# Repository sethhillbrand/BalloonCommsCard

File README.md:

# BalloonCommsCard
Dual-computer communications card designed to work with CSBF balloon flights

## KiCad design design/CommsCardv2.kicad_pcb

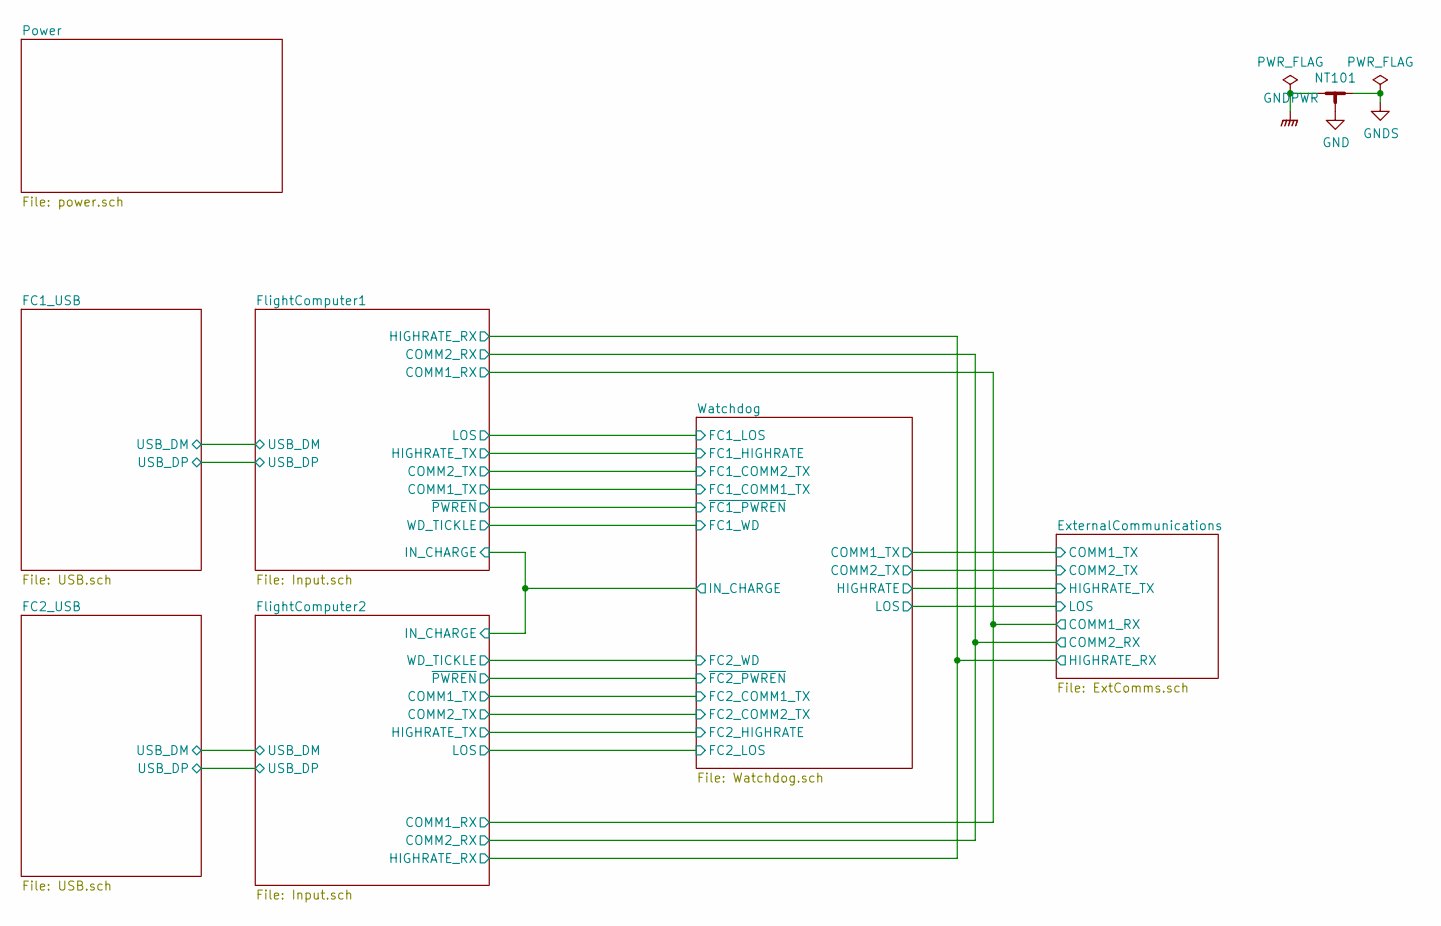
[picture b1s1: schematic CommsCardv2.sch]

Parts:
NT101: NP; NetTie-3_SMD_Pad2.0mm

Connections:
GND: NT101.3; also elsewhere on the board
GNDPWR: NT101.1; also elsewhere on the board

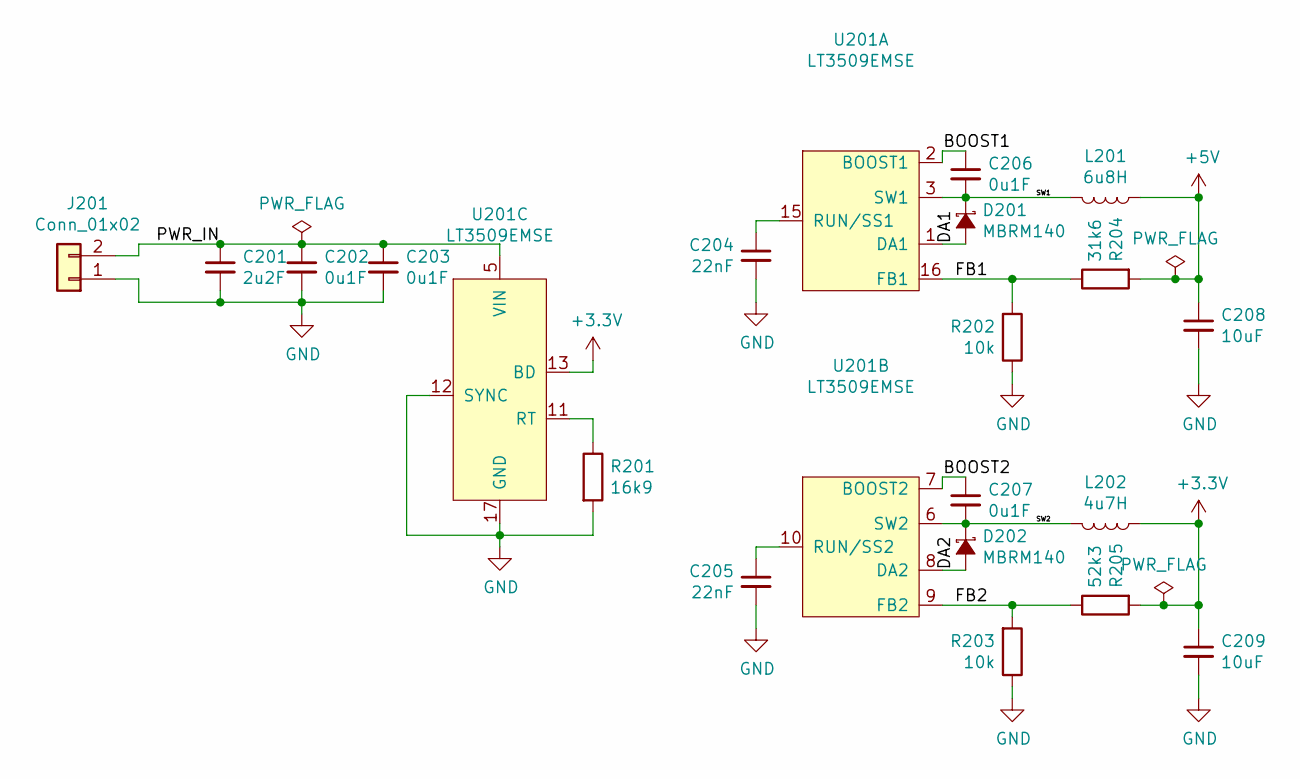
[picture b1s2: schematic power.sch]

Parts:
C201: 2u2F; C_0805_2012Metric; mpn UMK212BB7225KG-T
C202, C203, C206, C207: 0u1F; C_0603_1608Metric; mpn CL10B104KO8WPNC
C204, C205: 22nF; C_0603_1608Metric; mpn GRM188R71C223KA01D
C208, C209: 10uF; C_0805_2012Metric; mpn EMK212BB7106MG-T
D201, D202: MBRM140; D_Powermite2_AK; mpn MBRM140T3G
J201: Conn_01x02; PhoenixContact_MC_1,5_2-G-5.08_1x02_P5.08mm_Horizontal
L201: 6u8H; L_Abracon_ASPI-3012S; mpn ASPI-0315FS-6R8M-T2
L202: 4u7H; L_Abracon_ASPI-3012S; mpn ASPI-0315FS-4R7M-T2
R201: 16k9; R_0603_1608Metric; mpn ERJ-3EKF1692V
R202, R203: 10k; R_0603_1608Metric; mpn CRG0603J10K
R204: 31k6; R_0603_1608Metric; mpn CRCW060331K6FKEA
R205: 52k3; R_0603_1608Metric; mpn CRCW060352K3FKEA
U201: LT3509EMSE; MSOP-16-1EP_3x4mm_P0.5mm_EP1.65x2.85mm_ThermalVias; mpn LT3509EMSE#PBF

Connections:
+5V: C208.1, L201.1, R204.2; also elsewhere on the board
/Power/BOOST1: C206.1, U201.2 (BOOST1)
/Power/BOOST2: C207.1, U201.7 (BOOST2)
/Power/DA1: D201.2 (A), U201.1 (DA1)
/Power/DA2: D202.2 (A), U201.8 (DA2)
/Power/FB1: R202.2, R204.1, U201.16 (FB1)
/Power/FB2: R203.2, R205.1, U201.9 (FB2)
/Power/PWR_IN: C201.1, C202.1, C203.1, J201.2, U201.4 (VIN), U201.5 (VIN)
/Power/SW1: C206.2, D201.1 (K), L201.2, U201.3 (SW1)
/Power/SW2: C207.2, D202.1 (K), L202.2, U201.6 (SW2)
GND: C201.2, C202.2, C203.2, C204.2, C205.2, C208.2, C209.2, J201.1, R201.2, R202.1, R203.1, U201.12 (SYNC), U201.14 (GND), U201.17 (GND); also elsewhere on the board
unnamed: C204.1, U201.15 (RUN/SS1)
unnamed: C205.1, U201.10 (RUN/SS2)
unnamed: R201.1, U201.11 (RT)

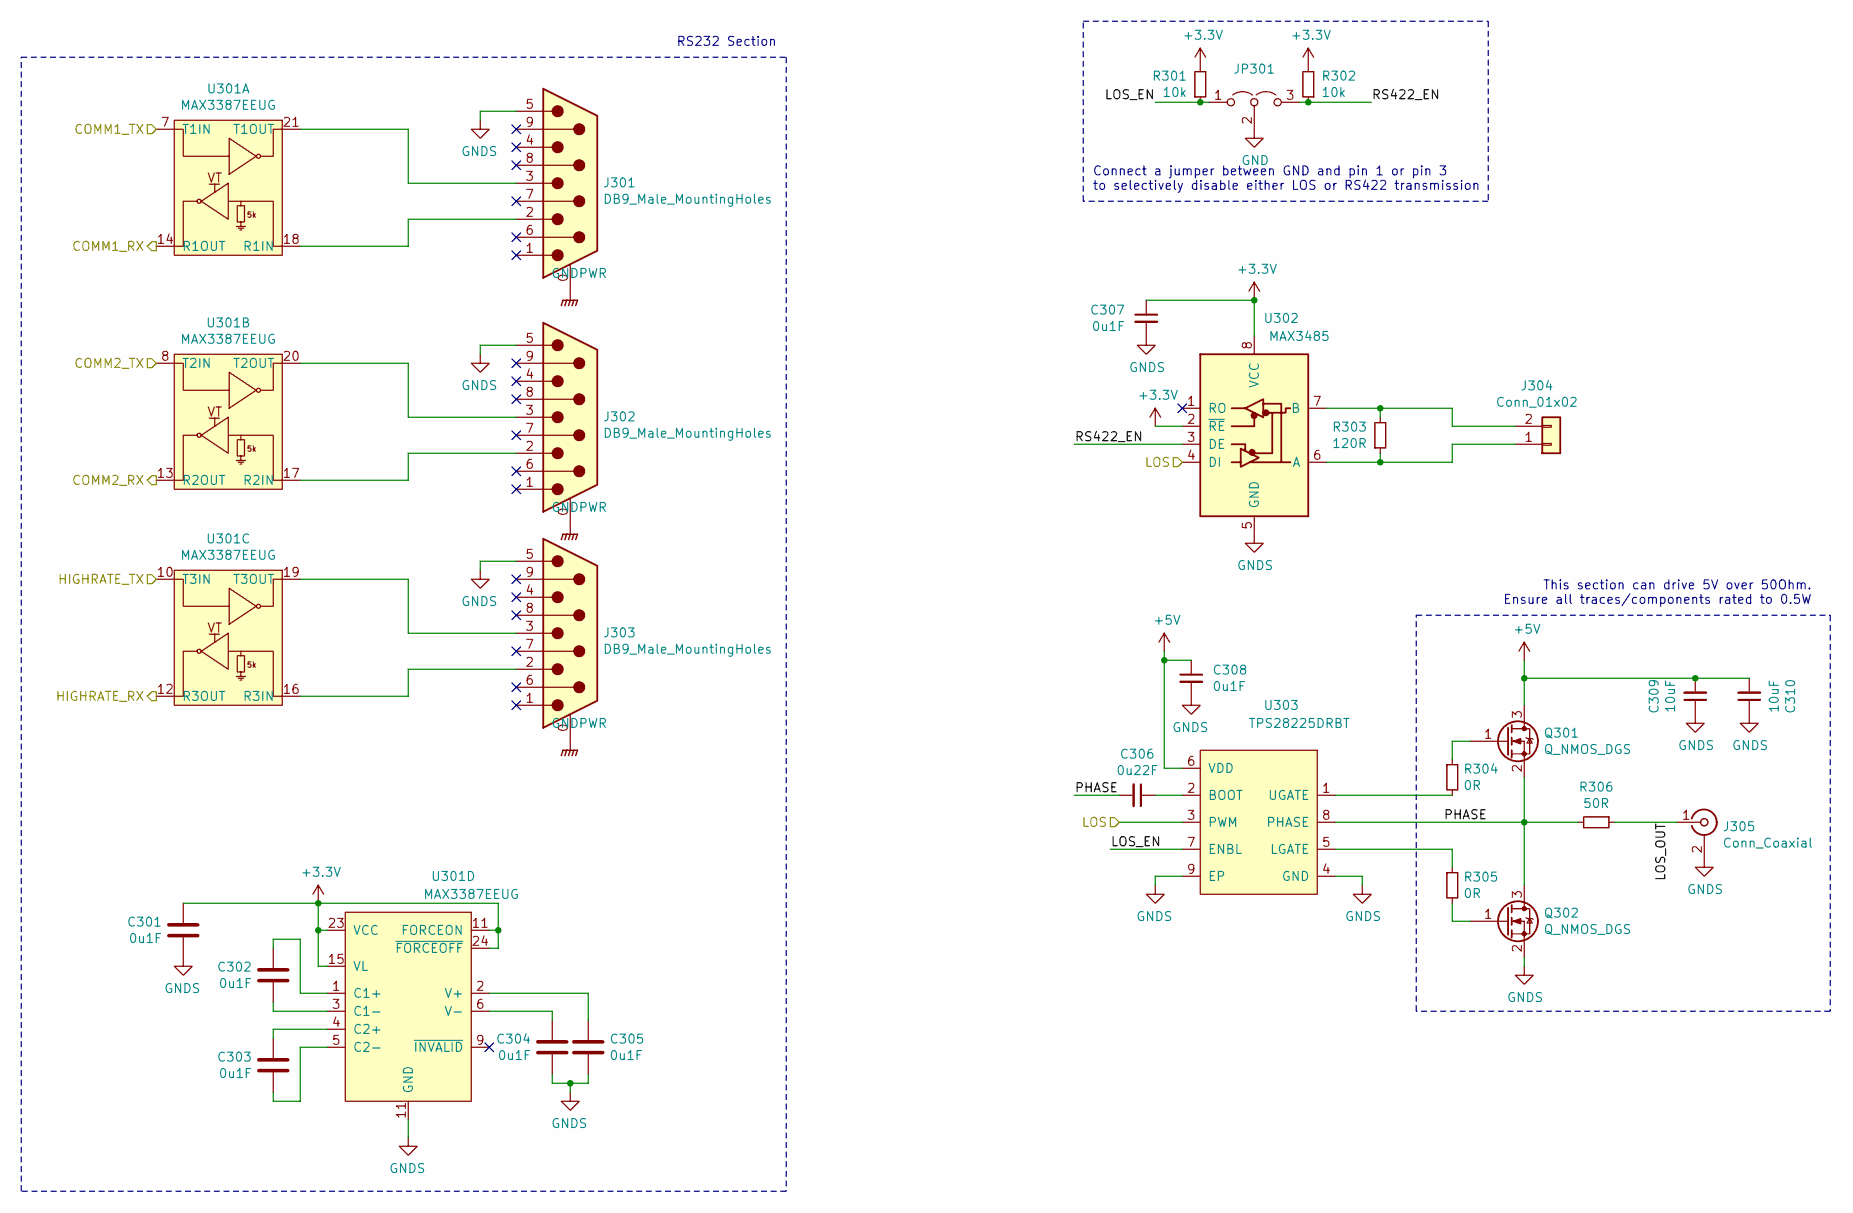
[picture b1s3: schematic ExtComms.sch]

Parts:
C301, C302, C303, C304, C305, C307, C308: 0u1F; C_0603_1608Metric; mpn CL10B104KO8WPNC
C306: 0u22F; C_0603_1608Metric; mpn GCM188R71E224KA55D
C309, C310: 10uF; C_0805_2012Metric; mpn EMK212BB7106MG-T
J301, J302, J303: DB9_Male_MountingHoles; DSUB-9_Male_Horizontal_P2.77x2.84mm_EdgePinOffset7.70mm_Hou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; mpn A-DF 09 A/KG-T2S
J304: Conn_01x02; PhoenixContact_MC_1,5_2-G-5.08_1x02_P5.08mm_Horizontal
J305: Conn_Coaxial; SMA_Molex_73251-1153_EdgeMount_Horizontal; mpn 0732512120
JP301: Jumper_NO_Small; PinHeader_1x03_P2.54mm_Vertical; mpn M20-9990345
Q301, Q302: Q_NMOS_DGS; SOT-23; mpn DMN2056U-7
R301, R302: 10k; R_0603_1608Metric; mpn CRG0603J10K
R303: 120R; R_0603_1608Metric; mpn RT0603DRE07120RL
R304, R305: 0R; R_1210_3225Metric; mpn RMCF1210ZT0R00
R306: 50R; R_2010_5025Metric; mpn RP92010T0050GTTR
U301: MAX3387EEUG; TSSOP-24_4.4x7.8mm_P0.65mm; mpn MAX3387EEUG+
U302: MAX3485; SOIC-8_3.9x4.9mm_P1.27mm; mpn MAX3485AEASA+
U303: TPS28225DRBT; Texas_S-PVSON-N8; mpn TPS28225DRBT

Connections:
+5V: C308.1, C309.2, C310.2, Q301.3 (D), U303.6 (VDD); also elsewhere on the board
/ExternalCommunications/COMM1_RX: U301.14 (R1OUT); also elsewhere on the board
/ExternalCommunications/COMM1_TX: U301.7 (T1IN); also elsewhere on the board
/ExternalCommunications/COMM2_RX: U301.13 (R2OUT); also elsewhere on the board
/ExternalCommunications/COMM2_TX: U301.8 (T2IN); also elsewhere on the board
/ExternalCommunications/HIGHRATE_RX: U301.12 (R3OUT); also elsewhere on the board
/ExternalCommunications/LOS: U302.4 (DI), U303.3 (PWM); also elsewhere on the board
/ExternalCommunications/LOS_EN: JP301.1 (A), R301.1, U303.7 (ENBL)
/ExternalCommunications/LOS_OUT: J305.1 (In), R306.1
/ExternalCommunications/PHASE: C306.2, Q301.2 (S), Q302.3 (D), R306.2, U303.8 (PHASE)
/ExternalCommunications/RS422_EN: JP301.3 (B), R302.1, U302.3 (DE)
/Watchdog/HIGHRATE: U301.10 (T3IN); also elsewhere on the board
GND: JP301.2 (C); also elsewhere on the board
GNDPWR: J301.0 (PAD), J302.0 (PAD), J303.0 (PAD); also elsewhere on the board
unnamed: C302.1, U301.1 (C1+)
unnamed: C302.2, U301.3 (C1-)
unnamed: C303.1, U301.4 (C2+)
unnamed: C303.2, U301.5 (C2-)
unnamed: C304.1, U301.6 (V-)
unnamed: C305.1, U301.2 (V+)
unnamed: C306.1, U303.2 (BOOT)
unnamed: J301.2, U301.18 (R1IN)
unnamed: J301.3, U301.21 (T1OUT)
unnamed: J302.2, U301.17 (R2IN)
unnamed: J302.3, U301.20 (T2OUT)
unnamed: J303.2, U301.16 (R3IN)
unnamed: J303.3, U301.19 (T3OUT)
unnamed: J304.1, R303.1, U302.6 (A)
unnamed: J304.2, R303.2, U302.7 (B)
unnamed: Q301.1 (G), R304.1
unnamed: Q302.1 (G), R305.2
unnamed: R304.2, U303.1 (UGATE)
unnamed: R305.1, U303.5 (LGATE)

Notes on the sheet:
This section can drive 5V over 50Ohm. Ensure all traces/components rated to 0.5W
Connect a jumper between GND and pin 1 or pin 3 to selectively disable either LOS or RS422 transmission
RS232 Section

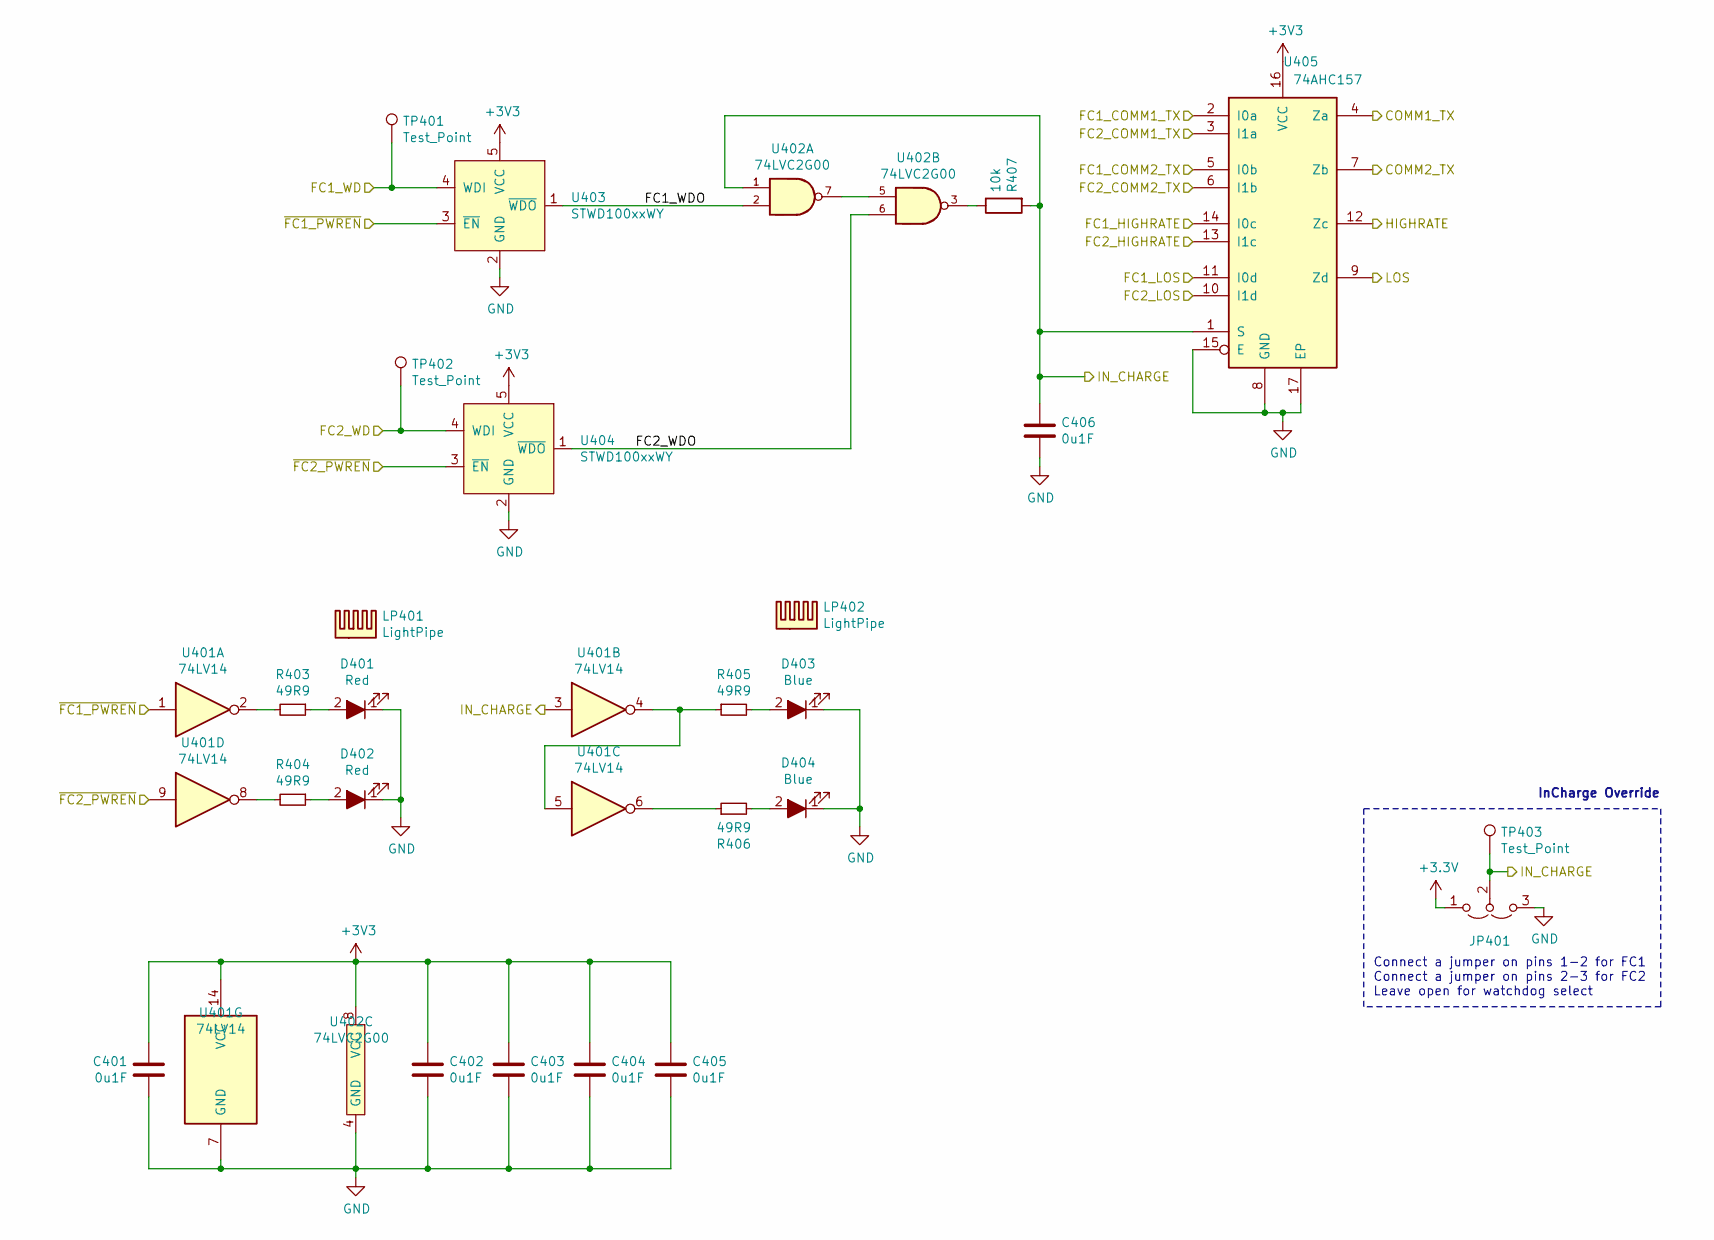
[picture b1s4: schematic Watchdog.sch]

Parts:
C401, C402, C403, C404, C405, C406: 0u1F; C_0603_1608Metric; mpn CL10B104KO8WPNC
D401, D402: Red; LED_1206_3216Metric; mpn 150120RS75000
D403, D404: Blue; LED_1206_3216Metric; mpn 150120BS75000
JP401: Jumper_NO_Small; PinHeader_1x03_P2.54mm_Vertical; mpn M20-9990345
LP401, LP402: LightPipe; Lumex_LPF-C012303S
R403, R404, R405, R406: 49R9; R_0603_1608Metric; mpn RNCP0603FTD49R9
R407: 10k; R_0603_1608Metric; mpn CRG0603J10K
TP401, TP402, TP403: Test_Point; TestPoint_Pad_D1.5mm
U401: 74LV14; TSSOP-14_4.4x5mm_P0.65mm; mpn SN74LV14APWR
U402: 74LVC2G00; VSSOP-8_2.3x2mm_P0.5mm; mpn SN74LVC2G00DCUR
U403, U404: STWD100xxWY; SOT-353_SC-70-5; mpn STWD100PYW83F
U405: 74AHC157; Texas_R-PVQFN-N16_EP4x3.5_Pitch0.5mm; mpn SN74AHC157RGYR

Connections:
/ExternalCommunications/COMM1_TX: U405.4 (Za); also elsewhere on the board
/ExternalCommunications/COMM2_TX: U405.7 (Zb); also elsewhere on the board
/ExternalCommunications/LOS: U405.9 (Zd); also elsewhere on the board
/FlightComputer1/COMM1_TX: U405.2 (I0a); also elsewhere on the board
/FlightComputer1/COMM2_TX: U405.5 (I0b); also elsewhere on the board
/FlightComputer1/IN_CHARGE: C406.1, JP401.2 (C), R407.2, TP403.1, U401.3, U402.1, U405.1 (S); also elsewhere on the board
/FlightComputer2/COMM1_TX: U405.3 (I1a); also elsewhere on the board
/FlightComputer2/COMM2_TX: U405.6 (I1b); also elsewhere on the board
/Watchdog/FC1_HIGHRATE: U405.14 (I0c); also elsewhere on the board
/Watchdog/FC1_LOS: U405.11 (I0d); also elsewhere on the board
/Watchdog/FC1_WD: TP401.1, U403.4 (WDI); also elsewhere on the board
/Watchdog/FC1_WDO: U402.2, U403.1 (~WDO)
/Watchdog/FC2_HIGHRATE: U405.13 (I1c); also elsewhere on the board
/Watchdog/FC2_LOS: U405.10 (I1d); also elsewhere on the board
/Watchdog/FC2_WD: TP402.1, U404.4 (WDI); also elsewhere on the board
/Watchdog/FC2_WDO: U402.6, U404.1 (~WDO)
/Watchdog/HIGHRATE: U405.12 (Zc); also elsewhere on the board
/Watchdog/~FC1_PWREN: U401.1, U403.3 (~EN); also elsewhere on the board
/Watchdog/~FC2_PWREN: U401.9, U404.3 (~EN); also elsewhere on the board
GND: C401.2, C402.2, C403.2, C404.2, C405.2, C406.2, D401.1 (K), D402.1 (K), D403.1 (K), D404.1 (K), JP401.3 (B), U401.7 (GND), U402.4 (GND), U403.2 (GND), U404.2 (GND), U405.8 (GND), U405.15 (E), U405.17 (EP); also elsewhere on the board
unnamed: D401.2 (A), R403.1
unnamed: D402.2 (A), R404.1
unnamed: D403.2 (A), R405.2
unnamed: D404.2 (A), R406.2
unnamed: R403.2, U401.2
unnamed: R404.2, U401.8
unnamed: R405.1, U401.4, U401.5
unnamed: R406.1, U401.6
unnamed: R407.1, U402.3
unnamed: U402.5, U402.7

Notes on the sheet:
Connect a jumper on pins 1-2 for FC1 Connect a jumper on pins 2-3 for FC2 Leave open for watchdog select
InCharge Override

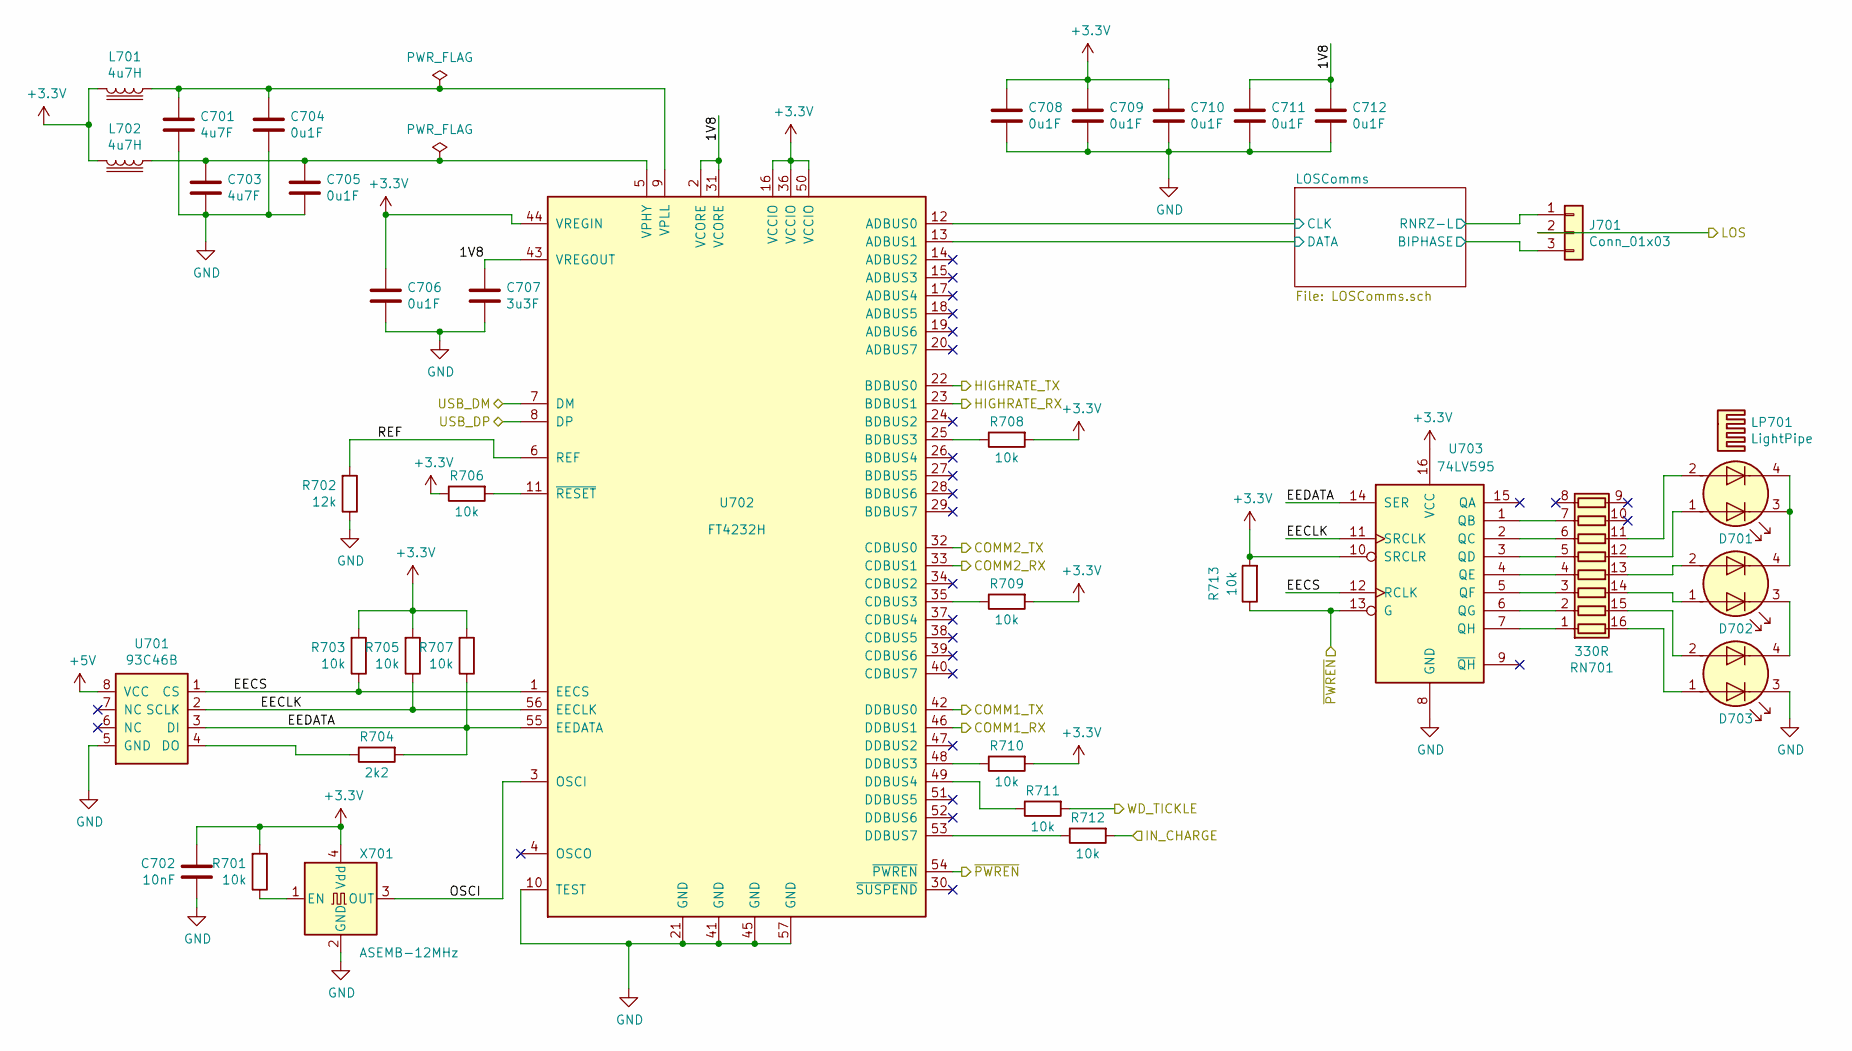
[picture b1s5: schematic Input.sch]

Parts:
C501, C503: 4u7F; C_0603_1608Metric; mpn CL10A475KQ8NNNC
C502: 10nF; C_0603_1608Metric; mpn CL10B103KO8NNNC
C504, C505, C506, C508, C509, C510, C511, C512: 0u1F; C_0603_1608Metric; mpn CL10B104KO8WPNC
C507: 3u3F; C_0603_1608Metric; mpn C1608X7S0G335M080AC
D501, D502, D503: LTST-C155GYKT; LED_RGB_1210; mpn LTST-C155GYKT
J501: Conn_01x03; PinHeader_1x03_P2.54mm_Vertical; mpn M20-9990345
L501, L502: 4u7H; R_1210_3225Metric; mpn 1277AS-H-4R7M=P2
LP501: LightPipe; LightPipe DiaLight 515-1064; mpn 5151064F
R501, R503, R505, R506, R507, R508, R509, R510, R511, R512, R513: 10k; R_0603_1608Metric; mpn CRG0603J10K
R502: 12k; R_0603_1608Metric; mpn CRG0603F12K
R504: 2k2; R_0603_1608Metric; mpn CRGH0603J2K2
RN501: 330R; R_Array_Convex_8x0402; mpn EXB-2HV331JV
U501: 93C46B; SOIC-8_3.9x4.9mm_P1.27mm; mpn 93C46BT-I/SN
U502: FT4232H; QFN-56-1EP_8x8mm_P0.5mm_EP4.5x5.2mm; mpn FT4232H-56Q-TRAY
U503: 74LV595; TSSOP-16_4.4x5mm_P0.65mm; mpn SN74LV595APWR
X501: ASEMB-12MHz; Oscillator_SMD_Abracon_ASE-4Pin_3.2x2.5mm; mpn ASEMB-12.000MHZ-XY-T

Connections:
+5V: U501.8 (VCC); also elsewhere on the board
/ExternalCommunications/COMM1_RX: U502.46 (DDBUS1); also elsewhere on the board
/ExternalCommunications/COMM2_RX: U502.33 (CDBUS1); also elsewhere on the board
/ExternalCommunications/HIGHRATE_RX: U502.23 (BDBUS1); also elsewhere on the board
/FC1_USB/USB_DM: U502.7 (DM); also elsewhere on the board
/FC1_USB/USB_DP: U502.8 (DP); also elsewhere on the board
/FlightComputer1/1V8: C507.1, C511.1, C512.1, U502.2 (VCORE), U502.31 (VCORE), U502.43 (VREGOUT)
/FlightComputer1/COMM1_TX: U502.42 (DDBUS0); also elsewhere on the board
/FlightComputer1/COMM2_TX: U502.32 (CDBUS0); also elsewhere on the board
/FlightComputer1/EECLK: R505.1, U501.2 (SCLK), U502.56 (EECLK), U503.11 (SRCLK)
/FlightComputer1/EECS: R503.1, U501.1 (CS), U502.1 (EECS), U503.12 (RCLK)
/FlightComputer1/EEDATA: R504.2, R507.1, U501.3 (DI), U502.55 (EEDATA), U503.14 (SER)
/FlightComputer1/IN_CHARGE: R512.2; also elsewhere on the board
/FlightComputer1/LOSComms/BIPHASE: J501.3; also elsewhere on the board
/FlightComputer1/LOSComms/CLK: U502.12 (ADBUS0); also elsewhere on the board
/FlightComputer1/LOSComms/DATA: U502.13 (ADBUS1); also elsewhere on the board
/FlightComputer1/LOSComms/RNRZ-L: J501.1; also elsewhere on the board
/FlightComputer1/OSCI: U502.3 (OSCI), X501.3 (OUT)
/FlightComputer1/REF: R502.2, U502.6 (REF)
/Watchdog/FC1_HIGHRATE: U502.22 (BDBUS0); also elsewhere on the board
/Watchdog/FC1_LOS: J501.2; also elsewhere on the board
/Watchdog/FC1_WD: R511.2; also elsewhere on the board
/Watchdog/~FC1_PWREN: R513.1, U502.54 (~PWREN), U503.13 (G); also elsewhere on the board
GND: C501.2, C502.2, C503.2, C504.2, C505.2, C506.2, C507.2, C508.2, C509.2, C510.2, C511.2, C512.2, D503.3 (K1), R502.1, U501.5 (GND), U502.10 (TEST), U502.21 (GND), U502.41 (GND), U502.45 (GND), U502.57 (GND), U503.8 (GND), X501.2 (GND); also elsewhere on the board
unnamed: C501.1, C504.1, L501.1, U502.9 (VPLL)
unnamed: C503.1, C505.1, L502.1, U502.5 (VPHY)
unnamed: D501.1 (A1), RN501.12 (R5.2)
unnamed: D501.2 (A2), RN501.11 (R6.2)
unnamed: D501.3 (K1), D501.4 (K2), D502.4 (K2)
unnamed: D502.1 (A1), RN501.14 (R3.2)
unnamed: D502.2 (A2), RN501.13 (R4.2)
unnamed: D502.3 (K1), D503.4 (K2)
unnamed: D503.1 (A1), RN501.16 (R1.2)
unnamed: D503.2 (A2), RN501.15 (R2.2)
unnamed: R501.1, X501.1 (EN)
unnamed: R504.1, U501.4 (DO)
unnamed: R506.2, U502.11 (~RESET)
unnamed: R508.1, U502.25 (BDBUS3)
unnamed: R509.1, U502.35 (CDBUS3)
unnamed: R510.1, U502.48 (DDBUS3)
unnamed: R511.1, U502.49 (DDBUS4)
unnamed: R512.1, U502.53 (DDBUS7)
unnamed: RN501.1 (R1.1), U503.7 (QH)
unnamed: RN501.2 (R2.1), U503.6 (QG)
unnamed: RN501.3 (R3.1), U503.5 (QF)
unnamed: RN501.4 (R4.1), U503.4 (QE)
unnamed: RN501.5 (R5.1), U503.3 (QD)
unnamed: RN501.6 (R6.1), U503.2 (QC)
unnamed: RN501.7 (R7.1), U503.1 (QB)

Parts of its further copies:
C701, C703: 4u7F; C_0603_1608Metric; mpn CL10A475KQ8NNNC
C702: 10nF; C_0603_1608Metric; mpn CL10B103KO8NNNC
C704, C705, C706, C708, C709, C710, C711, C712: 0u1F; C_0603_1608Metric; mpn CL10B104KO8WPNC
C707: 3u3F; C_0603_1608Metric; mpn C1608X7S0G335M080AC
D701, D702, D703: LTST-C155GYKT; LED_RGB_1210; mpn LTST-C155GYKT
J701: Conn_01x03; PinHeader_1x03_P2.54mm_Vertical; mpn M20-9990345
L701, L702: 4u7H; R_1210_3225Metric; mpn 1277AS-H-4R7M=P2
LP701: LightPipe; LightPipe DiaLight 515-1064; mpn 5151064F
R701, R703, R705, R706, R707, R708, R709, R710, R711, R712, R713: 10k; R_0603_1608Metric; mpn CRG0603J10K
R702: 12k; R_0603_1608Metric; mpn CRG0603F12K
R704: 2k2; R_0603_1608Metric; mpn CRGH0603J2K2
RN701: 330R; R_Array_Convex_8x0402; mpn EXB-2HV331JV
U701: 93C46B; SOIC-8_3.9x4.9mm_P1.27mm; mpn 93C46BT-I/SN
U702: FT4232H; QFN-56-1EP_8x8mm_P0.5mm_EP4.5x5.2mm; mpn FT4232H-56Q-TRAY
U703: 74LV595; TSSOP-16_4.4x5mm_P0.65mm; mpn SN74LV595APWR
X701: ASEMB-12MHz; Oscillator_SMD_Abracon_ASE-4Pin_3.2x2.5mm; mpn ASEMB-12.000MHZ-XY-T

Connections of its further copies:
+5V: U701.8 (VCC); also elsewhere on the board
/ExternalCommunications/COMM1_RX: U702.46 (DDBUS1); also elsewhere on the board
/ExternalCommunications/COMM2_RX: U702.33 (CDBUS1); also elsewhere on the board
/ExternalCommunications/HIGHRATE_RX: U702.23 (BDBUS1); also elsewhere on the board
/FC2_USB/USB_DM: U702.7 (DM); also elsewhere on the board
/FC2_USB/USB_DP: U702.8 (DP); also elsewhere on the board
/FlightComputer1/IN_CHARGE: R712.2; also elsewhere on the board
/FlightComputer2/1V8: C707.1, C711.1, C712.1, U702.2 (VCORE), U702.31 (VCORE), U702.43 (VREGOUT)
/FlightComputer2/COMM1_TX: U702.42 (DDBUS0); also elsewhere on the board
/FlightComputer2/COMM2_TX: U702.32 (CDBUS0); also elsewhere on the board
/FlightComputer2/EECLK: R705.1, U701.2 (SCLK), U702.56 (EECLK), U703.11 (SRCLK)
/FlightComputer2/EECS: R703.1, U701.1 (CS), U702.1 (EECS), U703.12 (RCLK)
/FlightComputer2/EEDATA: R704.2, R707.1, U701.3 (DI), U702.55 (EEDATA), U703.14 (SER)
/FlightComputer2/LOSComms/BIPHASE: J701.3; also elsewhere on the board
/FlightComputer2/LOSComms/CLK: U702.12 (ADBUS0); also elsewhere on the board
/FlightComputer2/LOSComms/DATA: U702.13 (ADBUS1); also elsewhere on the board
/FlightComputer2/LOSComms/RNRZ-L: J701.1; also elsewhere on the board
/FlightComputer2/OSCI: U702.3 (OSCI), X701.3 (OUT)
/FlightComputer2/REF: R702.2, U702.6 (REF)
/Watchdog/FC2_HIGHRATE: U702.22 (BDBUS0); also elsewhere on the board
/Watchdog/FC2_LOS: J701.2; also elsewhere on the board
/Watchdog/FC2_WD: R711.2; also elsewhere on the board
/Watchdog/~FC2_PWREN: R713.1, U702.54 (~PWREN), U703.13 (G); also elsewhere on the board
GND: C701.2, C702.2, C703.2, C704.2, C705.2, C706.2, C707.2, C708.2, C709.2, C710.2, C711.2, C712.2, D703.3 (K1), R702.1, U701.5 (GND), U702.10 (TEST), U702.21 (GND), U702.41 (GND), U702.45 (GND), U702.57 (GND), U703.8 (GND), X701.2 (GND); also elsewhere on the board
unnamed: C701.1, C704.1, L701.1, U702.9 (VPLL)
unnamed: C703.1, C705.1, L702.1, U702.5 (VPHY)
unnamed: D701.1 (A1), RN701.12 (R5.2)
unnamed: D701.2 (A2), RN701.11 (R6.2)
unnamed: D701.3 (K1), D701.4 (K2), D702.4 (K2)
unnamed: D702.1 (A1), RN701.14 (R3.2)
unnamed: D702.2 (A2), RN701.13 (R4.2)
unnamed: D702.3 (K1), D703.4 (K2)
unnamed: D703.1 (A1), RN701.16 (R1.2)
unnamed: D703.2 (A2), RN701.15 (R2.2)
unnamed: R701.1, X701.1 (EN)
unnamed: R704.1, U701.4 (DO)
unnamed: R706.2, U702.11 (~RESET)
unnamed: R708.1, U702.25 (BDBUS3)
unnamed: R709.1, U702.35 (CDBUS3)
unnamed: R710.1, U702.48 (DDBUS3)
unnamed: R711.1, U702.49 (DDBUS4)
unnamed: R712.1, U702.53 (DDBUS7)
unnamed: RN701.1 (R1.1), U703.7 (QH)
unnamed: RN701.2 (R2.1), U703.6 (QG)
unnamed: RN701.3 (R3.1), U703.5 (QF)
unnamed: RN701.4 (R4.1), U703.4 (QE)
unnamed: RN701.5 (R5.1), U703.3 (QD)
unnamed: RN701.6 (R6.1), U703.2 (QC)
unnamed: RN701.7 (R7.1), U703.1 (QB)

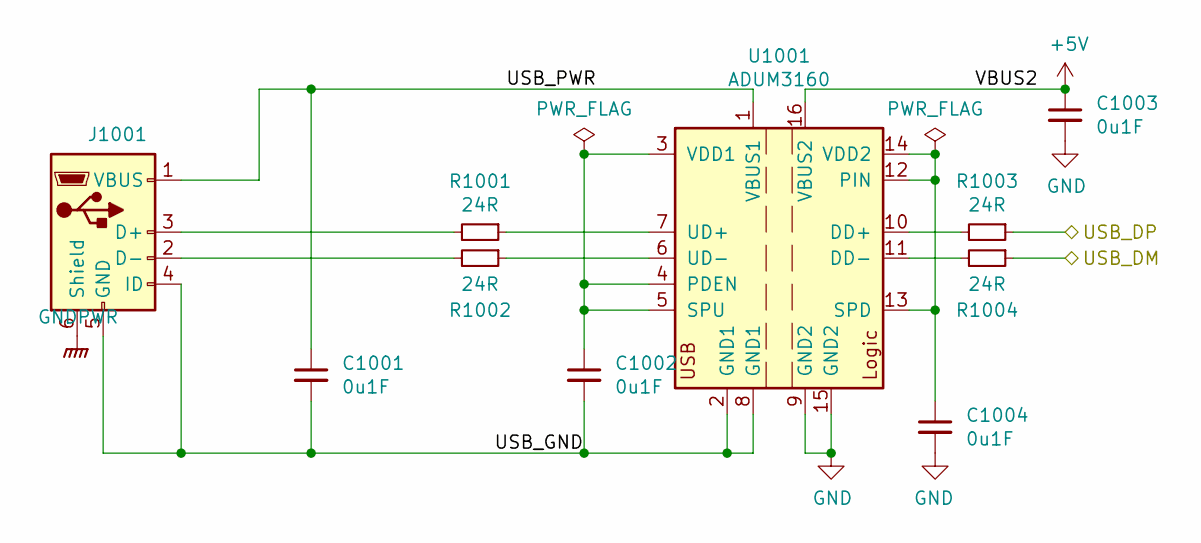
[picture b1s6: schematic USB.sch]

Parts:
C901, C902, C903, C904: 0u1F; C_0603_1608Metric; mpn CL10B104KO8WPNC
J901: USB_B; USB_Micro-B_Amphenol_10103594-0001LF_Horizontal; mpn 10103594-0001LF
R901, R902, R903, R904: 24R; R_0402_1005Metric; mpn ERA-2AKD240X
U901: ADUM3160; SOIC-16W_7.5x10.3mm_P1.27mm; mpn ADUM3160BRWZ-RL

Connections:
+5V: C903.1, U901.16 (VBUS2); also elsewhere on the board
/FC1_USB/USB_DM: R904.1; also elsewhere on the board
/FC1_USB/USB_DP: R903.1; also elsewhere on the board
/FC1_USB/USB_GND: C901.2, C902.2, J901.4 (ID), J901.5 (GND), U901.2 (GND1), U901.8 (GND1)
/FC1_USB/USB_PWR: C901.1, J901.1 (VBUS), U901.1 (VBUS1)
GND: C903.2, C904.2, U901.9 (GND2), U901.15 (GND2); also elsewhere on the board
GNDPWR: J901.6 (Shield); also elsewhere on the board
unnamed: C902.1, U901.3 (VDD1), U901.4 (PDEN), U901.5 (SPU)
unnamed: C904.1, U901.12 (PIN), U901.13 (SPD), U901.14 (VDD2)
unnamed: J901.2 (D-), R902.2
unnamed: J901.3 (D+), R901.2
unnamed: R901.1, U901.7 (UD+)
unnamed: R902.1, U901.6 (UD-)
unnamed: R903.2, U901.10 (DD+)
unnamed: R904.2, U901.11 (DD-)

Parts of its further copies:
C1001, C1002, C1003, C1004: 0u1F; C_0603_1608Metric; mpn CL10B104KO8WPNC
J1001: USB_B; USB_Micro-B_Amphenol_10103594-0001LF_Horizontal; mpn 10103594-0001LF
R1001, R1002, R1003, R1004: 24R; R_0402_1005Metric; mpn ERA-2AKD240X
U1001: ADUM3160; SOIC-16W_7.5x10.3mm_P1.27mm; mpn ADUM3160BRWZ-RL

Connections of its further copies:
+5V: C1003.1, U1001.16 (VBUS2); also elsewhere on the board
/FC2_USB/USB_DM: R1004.1; also elsewhere on the board
/FC2_USB/USB_DP: R1003.1; also elsewhere on the board
/FC2_USB/USB_GND: C1001.2, C1002.2, J1001.4 (ID), J1001.5 (GND), U1001.2 (GND1), U1001.8 (GND1)
/FC2_USB/USB_PWR: C1001.1, J1001.1 (VBUS), U1001.1 (VBUS1)
GND: C1003.2, C1004.2, U1001.9 (GND2), U1001.15 (GND2); also elsewhere on the board
GNDPWR: J1001.6 (Shield); also elsewhere on the board
unnamed: C1002.1, U1001.3 (VDD1), U1001.4 (PDEN), U1001.5 (SPU)
unnamed: C1004.1, U1001.12 (PIN), U1001.13 (SPD), U1001.14 (VDD2)
unnamed: J1001.2 (D-), R1002.2
unnamed: J1001.3 (D+), R1001.2
unnamed: R1001.1, U1001.7 (UD+)
unnamed: R1002.1, U1001.6 (UD-)
unnamed: R1003.2, U1001.10 (DD+)
unnamed: R1004.2, U1001.11 (DD-)
